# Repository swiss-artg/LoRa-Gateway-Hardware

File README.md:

# LoRa-Gateway-Hardware
KiCad sources for a RaspberryPi LoRa Gateway HAT

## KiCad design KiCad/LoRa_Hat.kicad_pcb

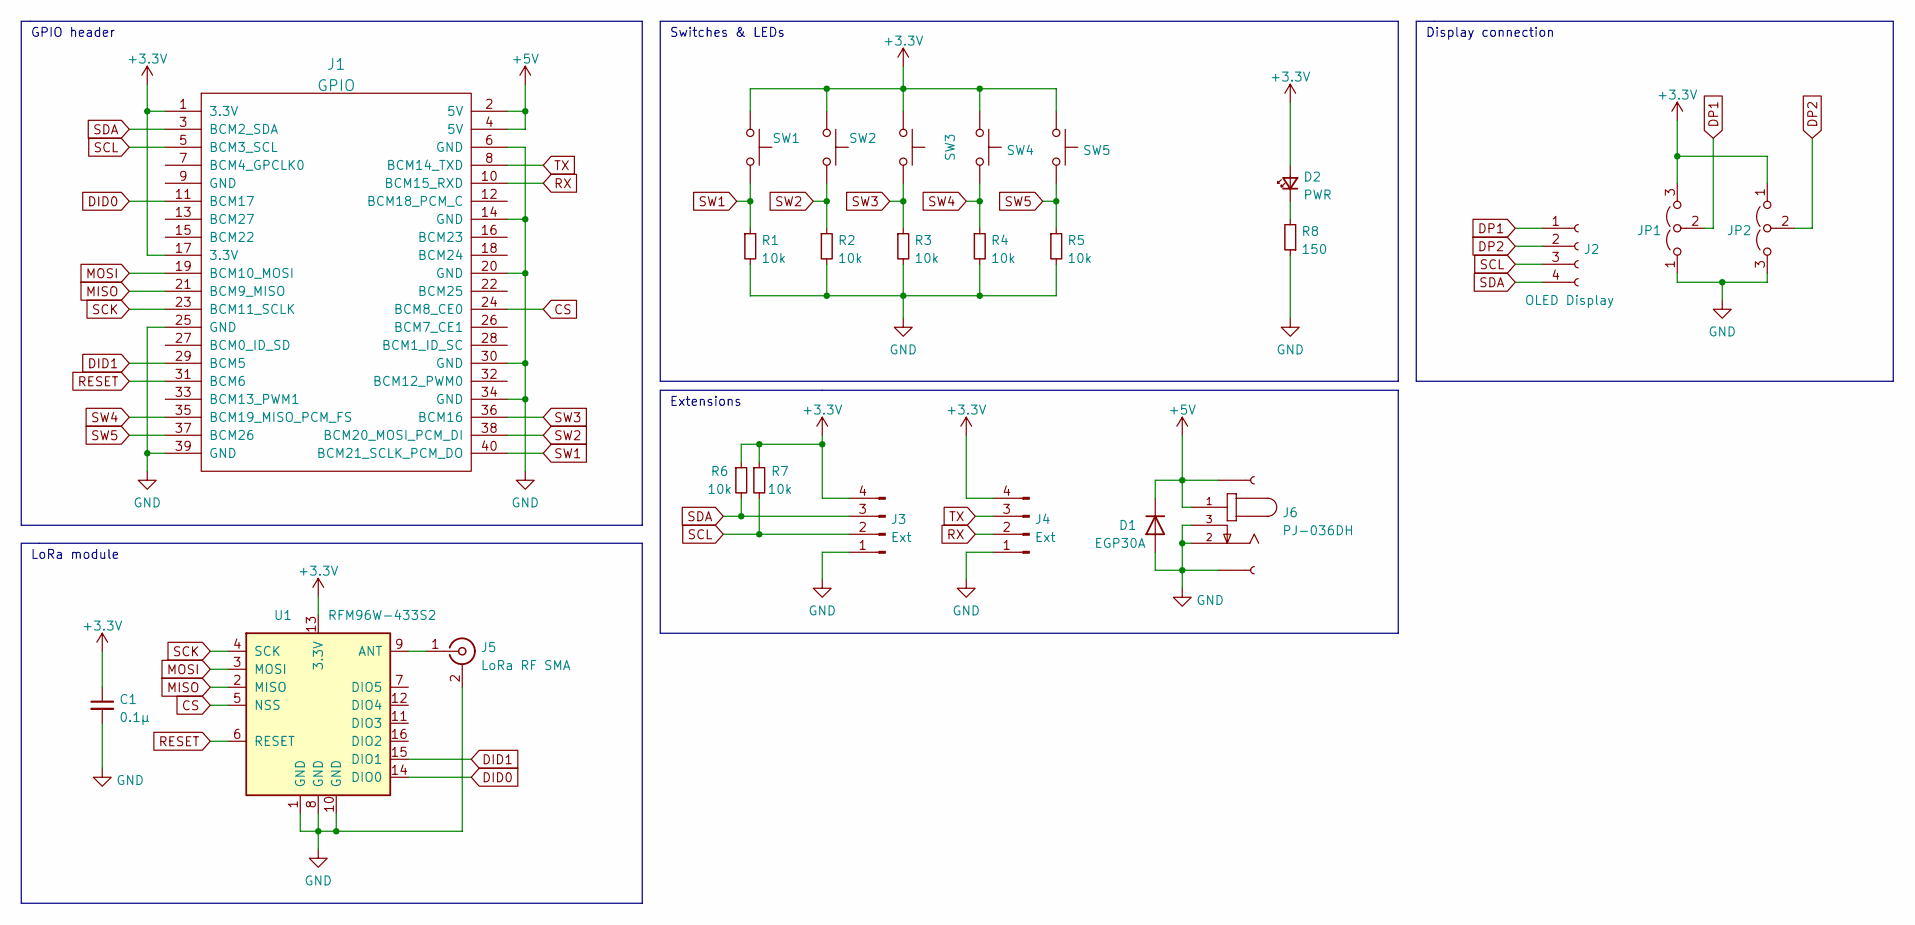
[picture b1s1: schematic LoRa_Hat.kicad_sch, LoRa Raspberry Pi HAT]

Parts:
C1: 0.1µ; C_Disc_D3.8mm_W2.6mm_P2.50mm; Manufacturer Part No. RCER71H104K0A2H03B; LCSC Part Number C14663
D1: EGP30A; D_DO-201AD_P15.24mm_Horizontal; Manufacturer Part No. EGP30A; Digikey Part No. EGP30ACT-ND
D2: PWR; LED_D3.0mm; Manufacturer Part No. TLHG4405; Digikey Part No. 751-1101-ND
J1: GPIO; PinSocket_2x20_P2.54mm_Vertical; Manufacturer Part No. 61304021821 / PPTC202LFBN-RC; Digikey Part No. S6104-ND
J2: OLED Display; OLED_Display
J3, J4: Ext; PinHeader_1x04_P2.54mm_Horizontal; Manufacturer Part No. M20-9750446; Digikey Part No. 952-1965-ND
J5: LoRa RF SMA; SMA_RFSolutions_EDGE
J6: PJ-036DH; Manufacturer Part No. PJ-036DH; Digikey Part No. CP-036DH-ND
J7, J8: Conn_01x01_Female; SolderWire
JP1, JP2: Jumper_3_Bridged12; SolderJumper-3_P1.3mm_Open_RoundedPad1.0x1.5mm
R1, R2, R3, R4, R5: 10k; R_Axial_DIN0207_L6.3mm_D2.5mm_P7.62mm_Horizontal; Manufacturer Part No. CFR25J10K; LCSC Part Number C25819
R6, R7: 10k; R_Axial_DIN0207_L6.3mm_D2.5mm_P7.62mm_Horizontal; Manufacturer Part No. CFR25J10K; LCSC Part Number C25804
R8: 150; R_Axial_DIN0207_L6.3mm_D2.5mm_P7.62mm_Horizontal; Manufacturer Part No. MFR-25FBF52-150R; LCSC Part Number C4177
SW1, SW2, SW3, SW4, SW5: SW_Push; SW_PUSH_6mm_H4.3mm; Manufacturer Part No. TS02-66-50-BK-100-SCR-D; Digikey Part No. 2223-TS02-66-50-BK-100-SCR-D-ND
U1: RFM96W-433S2; HOPERF_RFM9XW_SMD

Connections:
+3V3: C1.1, D2.2 (A), J1.1 (3.3V), J1.17 (3.3V), J3.4, J4.4, JP1.3 (B), JP2.1 (A), R6.1, R7.1, SW1.1, SW2.1, SW3.1, SW4.1, SW5.1, U1.13 (3.3V)
+5V: D1.1 (K), J1.2 (5V), J1.4 (5V), J6.1, J7.1
CS: J1.24 (BCM8_CE0), U1.5 (NSS)
DID0: J1.11 (BCM17), U1.14 (DIO0)
DID1: J1.29 (BCM5), U1.15 (DIO1)
DP1: J2.1, JP1.2 (C)
DP2: J2.2, JP2.2 (C)
GND: C1.2, D1.2 (A), J1.6 (GND), J1.14 (GND), J1.20 (GND), J1.25 (GND), J1.30 (GND), J1.34 (GND), J1.39 (GND), J3.1, J4.1, J5.2 (Ext), J6.2, J6.3, J8.1, JP1.1 (A), JP2.3 (B), R1.2, R2.2, R3.2, R4.2, R5.2, R8.1, U1.1 (GND), U1.8 (GND), U1.10 (GND)
MISO: J1.21 (BCM9_MISO), U1.2 (MISO)
MOSI: J1.19 (BCM10_MOSI), U1.3 (MOSI)
unnamed: D2.1 (K), R8.2
unnamed: J5.1 (In), U1.9 (ANT)
RESET: J1.31 (BCM6), U1.6 (RESET)
RX: J1.10 (BCM15_RXD), J4.2
SCK: J1.23 (BCM11_SCLK), U1.4 (SCK)
SCL: J1.5 (BCM3_SCL), J2.3, J3.2, R7.2
SDA: J1.3 (BCM2_SDA), J2.4, J3.3, R6.2
SW1: J1.40 (BCM21_SCLK_PCM_DO), R1.1, SW1.2
SW2: J1.38 (BCM20_MOSI_PCM_DI), R2.1, SW2.2
SW3: J1.36 (BCM16), R3.1, SW3.2
SW4: J1.35 (BCM19_MISO_PCM_FS), R4.1, SW4.2
SW5: J1.37 (BCM26), R5.1, SW5.2
TX: J1.8 (BCM14_TXD), J4.3

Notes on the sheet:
LoRa module
GPIO header
Switches & LEDs
Display connection
Extensions

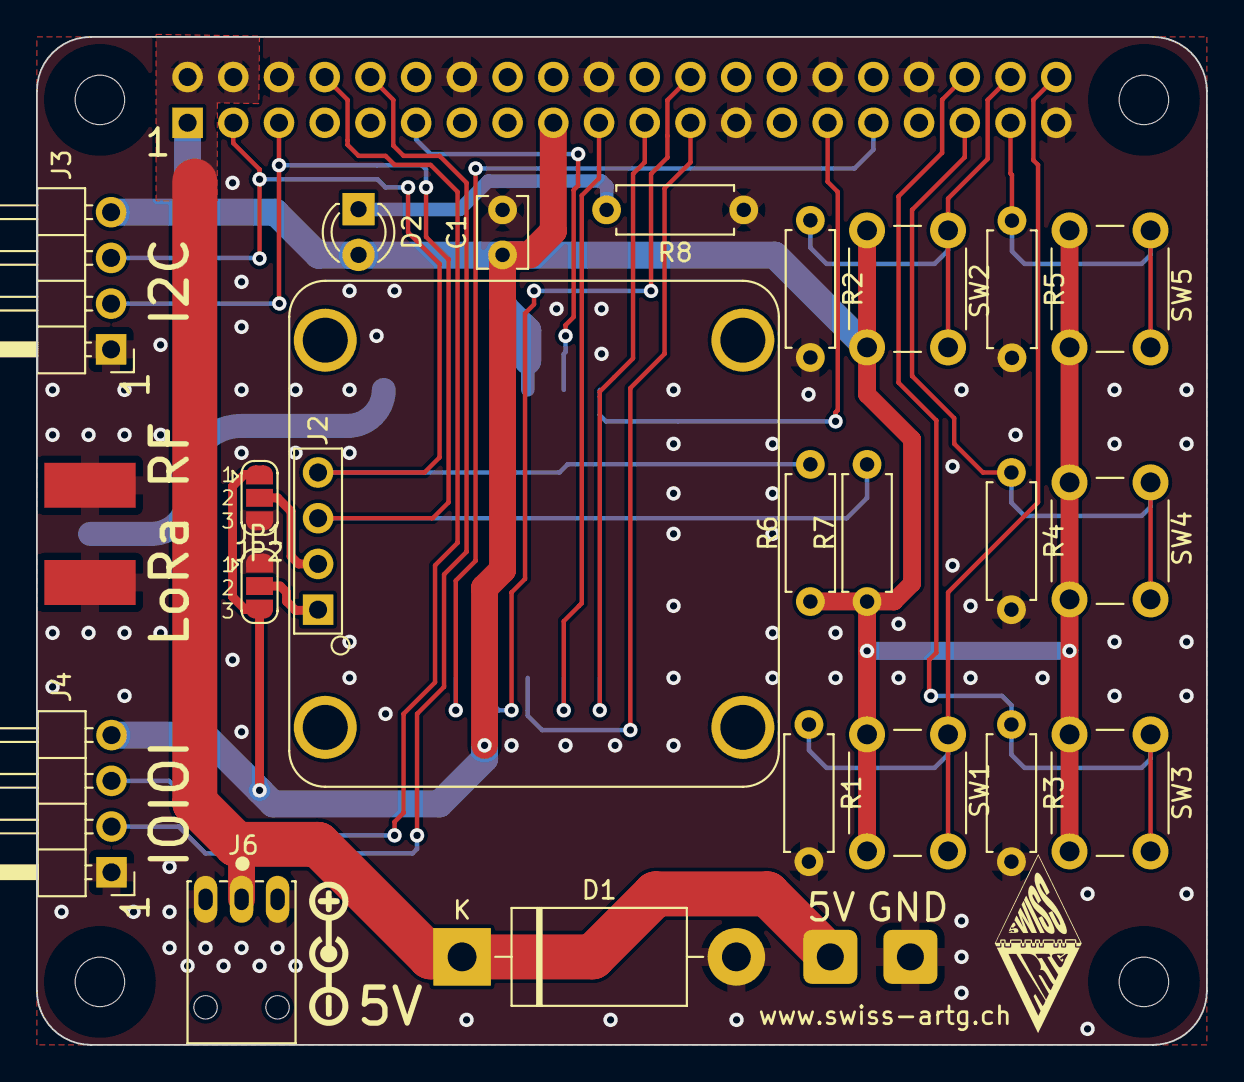
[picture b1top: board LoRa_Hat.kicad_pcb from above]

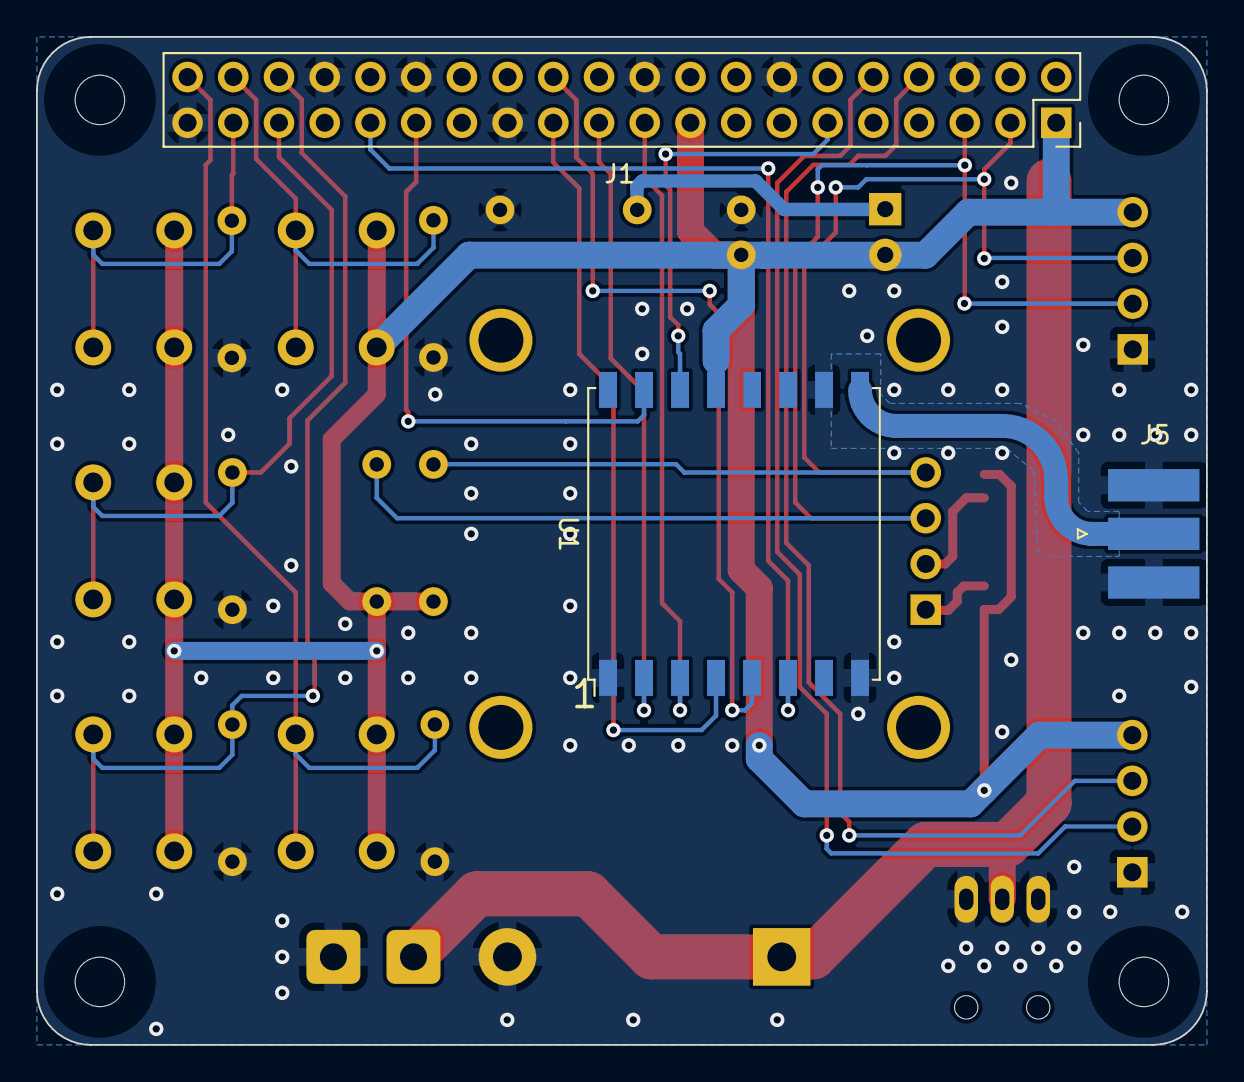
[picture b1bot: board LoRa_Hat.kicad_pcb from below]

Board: 2 copper layers, 65.0 x 56.0 mm, 27 parts (3 on the bottom side), 23 nets.

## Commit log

2024-01-19 Initial commit
    Version 2
2024-01-19 More structure
2024-09-19 Schema corrections for J1 and J2 to reflect PCB silk layer print
